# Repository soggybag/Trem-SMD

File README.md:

# Trem (SMD)

A tremolo for guitar in a Hammond 1590B: a TL064 LFO with SHAPE and SQ/TRI, driving a **discrete LM3086-style transistor VCA**. SMD parts are assembled by JLCPCB; the pots, toggle and LED are hand-soldered on the back (panel side).

## Controls

| Control | Part | Function |
|---|---|---|
| RATE | RV1 A10k | LFO speed, ~2–17 Hz (measured) |
| SHAPE | RV2 B100k | LFO skew: ramp up ↔ triangle ↔ ramp down |
| DEPTH | RV3 B100k | Tremolo depth, up to full cut |
| SQ/TRI | SW1 | Square or triangle LFO |
| Balance (trim) | RV4 2k (v2.1: symmetric, wiper to VA) | Nulls the LFO "thump" bleed |

Note: on this revision RATE and DEPTH turn backwards (fully CCW = fast / max) because the back-mounted pots mirror lugs 1 and 3. Fix planned for the next revision.

## How it works

- **LFO:** U1D integrator + U1C Schmitt trigger make the triangle and square. RATE sets the drive level; diodes D3/D4 with SHAPE set separate rise and fall rates.
- **Control:** DEPTH → U1A (inverting, offset by R13) sets the VCA tail current through R14.
- **Audio:** Q1 (MMBT5089) preamp → ÷48 → Q2 differential pair (gain ∝ tail current) → Q3 pair + Q4 PNP output amp → OUT.
- A reusable write-up of the VCA: [docs/VCA Building Block.md](docs/VCA%20Building%20Block.md).

Schematic: [Trem_23_schematic.pdf](Trem_23_schematic.pdf) · Layout: [Trem_23_layout.pdf](Trem_23_layout.pdf)

## Build notes

- **Hand-soldered (back side):** RATE/SHAPE/DEPTH 16 mm pots, SW1 (**sub-miniature** SPDT, 2.54 mm pitch, e.g. Taiway 200MSP1T1B1M1QE or Dailywell 2MS1; standard mini toggles do not fit), the LED, and the wire pads.
- Power: 9 V centre-negative; SS14 series reverse-polarity protection; ~3.2 mA (+ LED).
- Set RV4 for minimum LFO bleed at OUT (DEPTH max, no input, scope at 10 mV/div).
- Details: [docs/Build Notes.md](docs/Build%20Notes.md).

## Status

- Boards received from JLCPCB 2026-10-01; bench tested 2026-10-02. DC, LFO and VCA all verified, and it sounds good with a guitar. See [docs/Test Procedure.md](docs/Test%20Procedure.md).
- Next revision: bigger wiring pads or a 1×4 header, pot lug swap, RATE/DEPTH spacing (maybe 9 mm pots), toggle to the other side, LFO-rate LED idea. Roadmap: [Trem Roadmap.md](Trem%20Roadmap.md).

## Repository layout

```
Trem_23.kicad_pro / .kicad_sch / .kicad_pcb / .kicad_dru   KiCad 10 project
Trem.pretty/, fp-lib-table                              project footprints
3dmodels/          pot, switch and enclosure models (${KIPRJMOD})
docs/              test procedure, build notes, VCA write-up
enclosure/         panel art (Affinity + PDF/SVG exports)
*.pdf, *.png       schematic, layout and renders
```

Opens with KiCad 10. Libraries and 3D models are project-local or from KiCad's standard library.

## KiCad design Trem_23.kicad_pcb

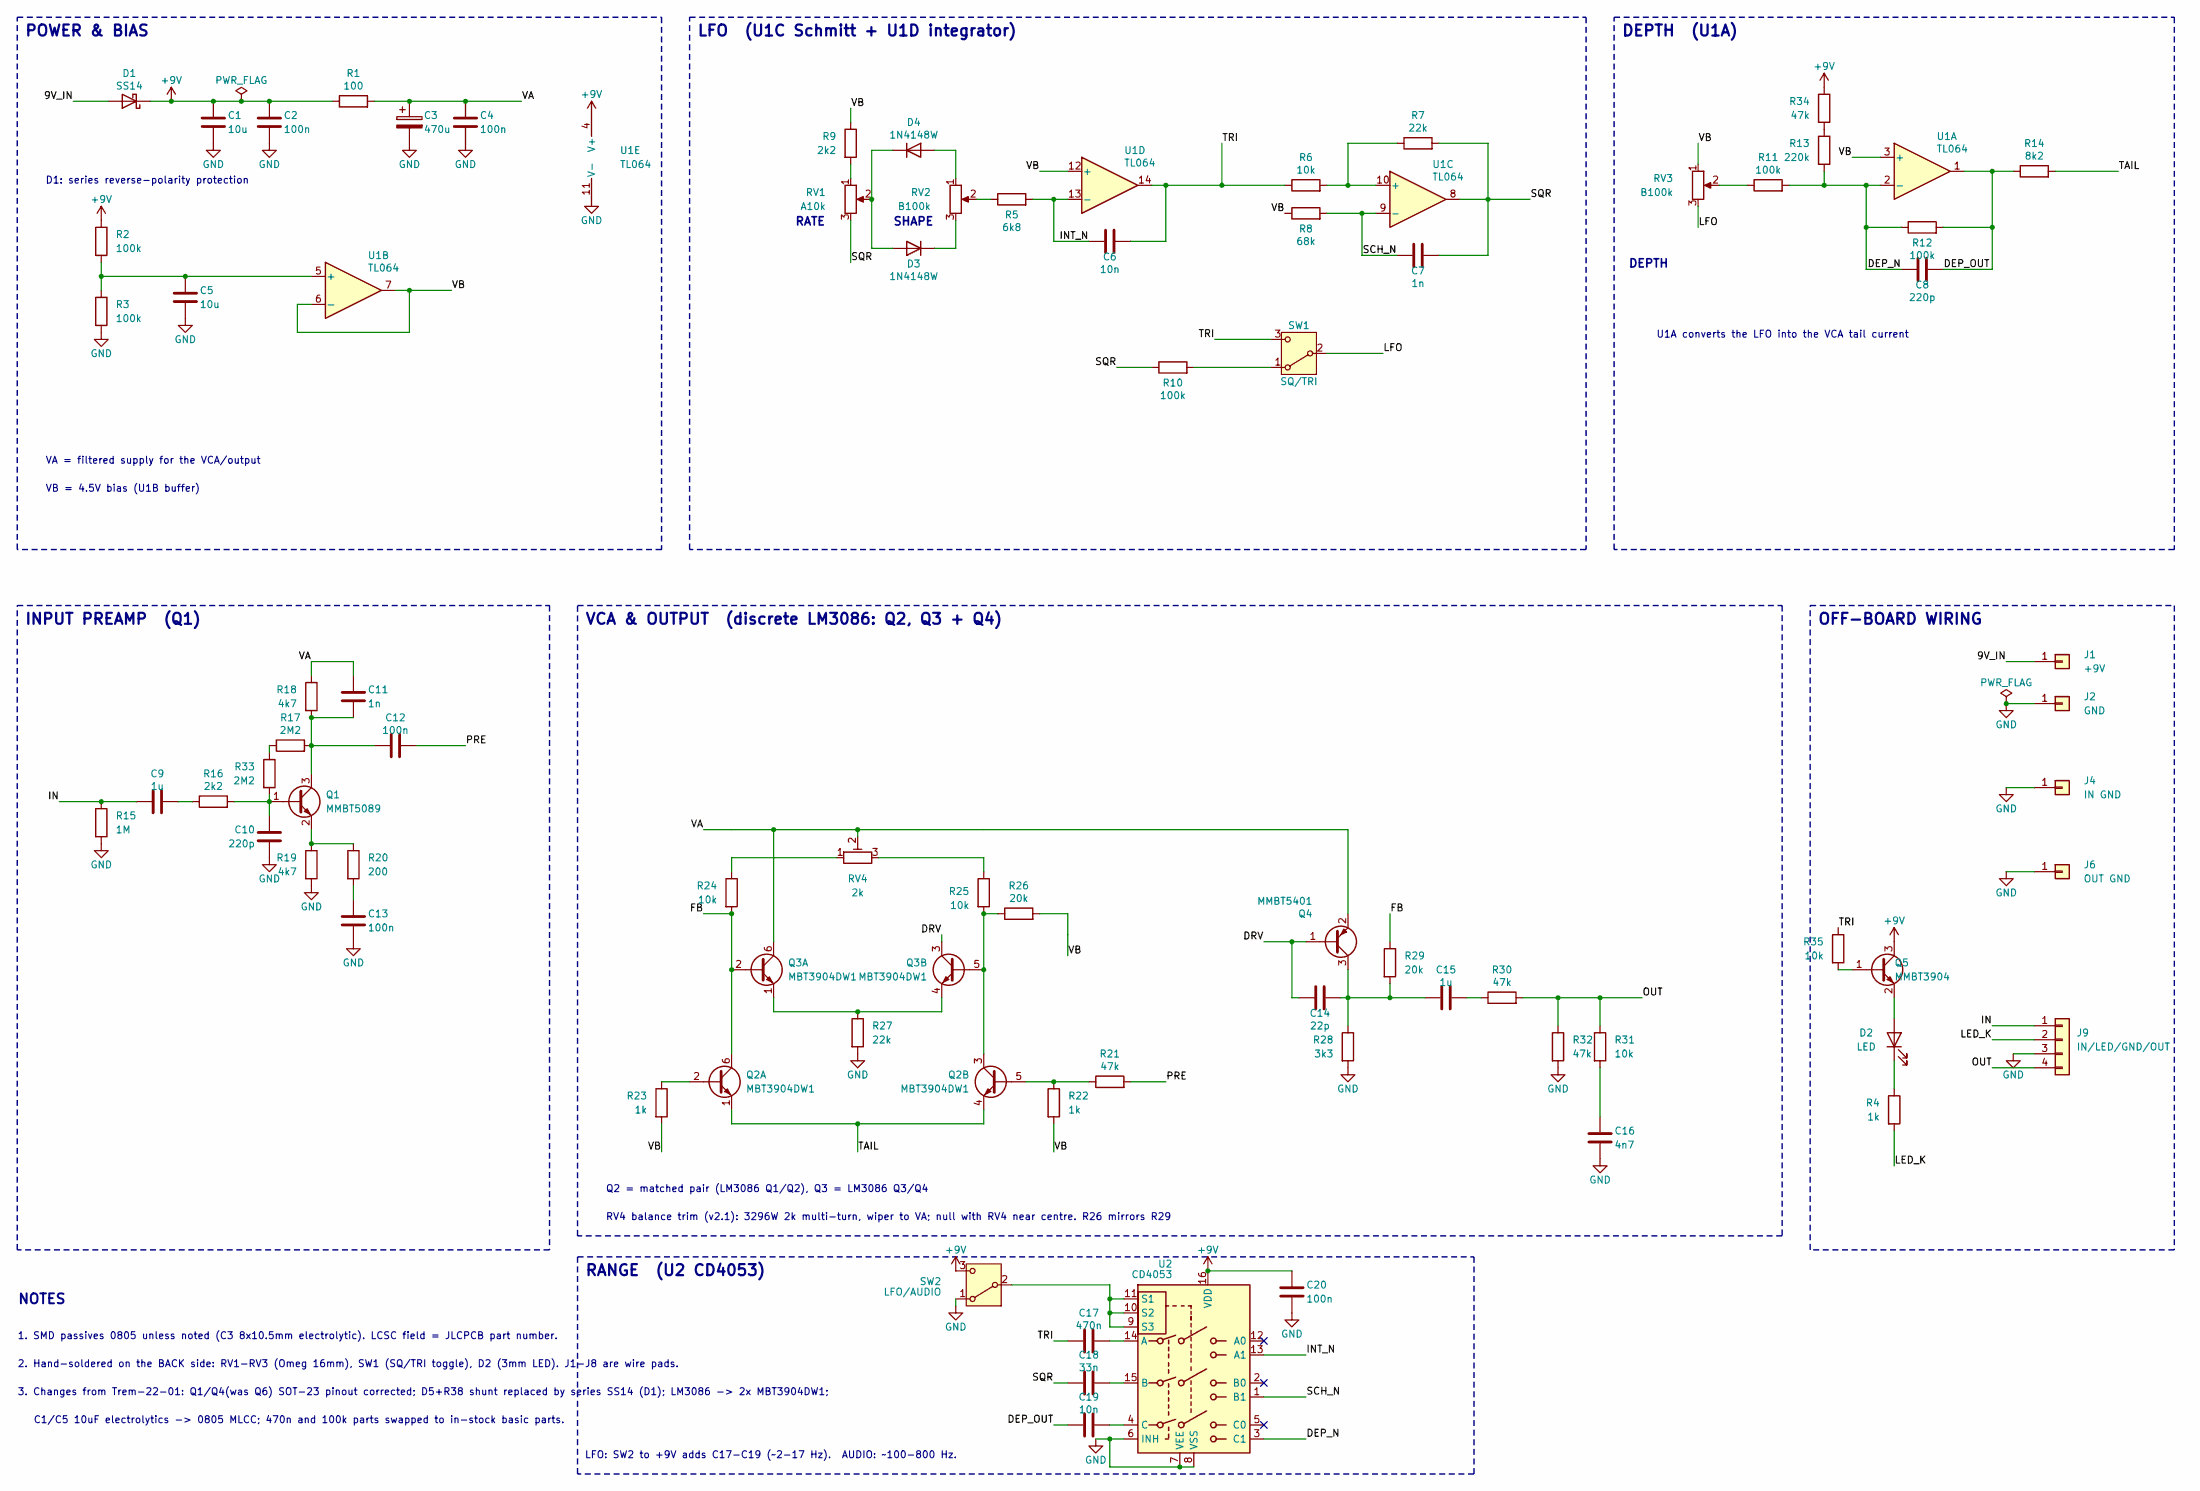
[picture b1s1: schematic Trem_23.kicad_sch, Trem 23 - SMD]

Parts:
C1, C5: 10u; C_0805_2012Metric; LCSC C15850
C2, C4, C12, C13: 100n; C_0805_2012Metric; LCSC C49678
C3: 470u; CP_Radial_D8.0mm_P3.50mm; LCSC C970706
C6: 10n; C_0805_2012Metric; LCSC C1710
C7, C11: 1n; C_0805_2012Metric; LCSC C46653
C8, C10: 220p; C_0805_2012Metric; LCSC C107145
C9, C15: 1u; C_0805_2012Metric; LCSC C28323
C14: 22p; C_0805_2012Metric; LCSC C1804
C16: 4n7; C_0805_2012Metric; LCSC C1744
C17: 470n; C_0805_2012Metric_Pad1.18x1.45mm_HandSolder; LCSC C13967
C18: 33n; C_0805_2012Metric_Pad1.18x1.45mm_HandSolder; LCSC C1739
C19: 10n; C_0805_2012Metric_Pad1.18x1.45mm_HandSolder; LCSC C1710
C20: 100n; C_0805_2012Metric_Pad1.18x1.45mm_HandSolder; LCSC C49678
D1: SS14; D_SMA; LCSC C2480
D2: LED; LED_D3.0mm
D3, D4: 1N4148W; D_SOD-123; LCSC C81598
J1: +9V; SolderWire-0.5sqmm_1x01_D0.9mm_OD2.1mm
J2: GND; SolderWire-0.5sqmm_1x01_D0.9mm_OD2.1mm
J4: IN GND; SolderWire-0.5sqmm_1x01_D0.9mm_OD2.1mm
J6: OUT GND; SolderWire-0.5sqmm_1x01_D0.9mm_OD2.1mm
J9: IN/LED/GND/OUT; PinHeader_1x04_P2.54mm_Vertical
Q1: MMBT5089; SOT-23; LCSC C116160
Q2, Q3: MBT3904DW1; SOT-363_SC-70-6; LCSC C110150
Q4: MMBT5401; SOT-23; LCSC C8326
Q5: MMBT3904; SOT-23; LCSC C20526
R1: 100; R_0805_2012Metric; LCSC C17408
R2, R3, R10, R11, R12: 100k; R_0805_2012Metric; LCSC C149504
R4, R22, R23: 1k; R_0805_2012Metric; LCSC C17513
R5: 6k8; R_0805_2012Metric; LCSC C17772
R6, R24, R25, R31: 10k; R_0805_2012Metric; LCSC C17414
R7, R27: 22k; R_0805_2012Metric; LCSC C17560
R8: 68k; R_0805_2012Metric; LCSC C17801
R9, R16: 2k2; R_0805_2012Metric; LCSC C17520
R13: 220k; R_0805_2012Metric; LCSC C17556
R14: 8k2; R_0805_2012Metric; LCSC C17828
R15: 1M; R_0805_2012Metric; LCSC C17514
R17: 2M2; R_0805_2012Metric; LCSC C26113
R18, R19: 4k7; R_0805_2012Metric; LCSC C17673
R20: 200; R_0805_2012Metric; LCSC C17540
R21, R30, R32: 47k; R_0805_2012Metric; LCSC C17713
R26, R29: 20k; R_0805_2012Metric; LCSC C4328
R28: 3k3; R_0805_2012Metric; LCSC C26010
R33: 2M2; R_0805_2012Metric_Pad1.20x1.40mm_HandSolder; LCSC C26113
R34: 47k; R_0805_2012Metric_Pad1.20x1.40mm_HandSolder; LCSC C17713
R35: 10k; R_0805_2012Metric_Pad1.20x1.40mm_HandSolder; LCSC C17414
RV1: A10k; Potentiometer_Alpha_RD901F-40-00D_Single_Vertical
RV2, RV3: B100k; Potentiometer_Alpha_RD901F-40-00D_Single_Vertical
RV4: 2k; Potentiometer_Bourns_3314J_Vertical; LCSC C94513
SW1: SQ/TRI; SW_Taiway_200_SPDT
SW2: LFO/AUDIO; SW_Taiway_200_SPDT
U1: TL064; SOIC-14_3.9x8.7mm_P1.27mm; LCSC C402159
U2: CD4053; SOIC-16_3.9x9.9mm_P1.27mm; LCSC C6742

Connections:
/9V_IN: D1.2 (A), J1.1
/DEP_N: C8.1, R11.2, R12.1, R13.2, U1.2 (-), U2.3 (C1)
/DEP_OUT: C8.2, C19.1, R12.2, R14.1, U1.1
/DRV: C14.1, Q3.3 (C2), Q4.1 (B)
/FB: Q2.6 (C1), Q3.2 (B1), R24.2, R29.1
/IN: C9.1, J9.1, R15.1
/INT_N: C6.1, R5.2, U1.13 (-), U2.13 (A1)
/LED_K: J9.2, R4.2
/LFO: RV3.3, SW1.2 (B)
/OUT: J9.4, R30.2, R31.1, R32.1
/PRE: C12.2, R21.2
/SCH_N: C7.1, R8.2, U1.9 (-), U2.1 (B1)
/SQR: C7.2, C18.1, R7.2, R10.1, RV1.3, U1.8
/TAIL: Q2.1 (E1), Q2.4 (E2), R14.2
/TRI: C6.2, C17.1, R6.1, R35.1, SW1.3 (C), U1.14
/VA: C3.1, C4.1, C11.1, Q3.6 (C1), Q4.2 (E), R1.2, R18.1, RV4.2
/VB: R8.1, R9.1, R22.2, R23.2, R26.2, RV3.1, U1.3 (+), U1.6 (-), U1.7, U1.12 (+)
unnamed: C9.2, R16.1
unnamed: C13.1, R20.2
unnamed: C15.2, R30.1
unnamed: C16.1, R31.2
unnamed: D2.2 (A), Q5.2 (E)
unnamed: D2.1 (K), R4.1
unnamed: D3.2 (A), D4.1 (K), RV1.2
unnamed: D3.1 (K), RV2.3
unnamed: D4.2 (A), RV2.1
unnamed: C10.1, Q1.1 (B), R16.2, R33.2
unnamed: C11.2, C12.1, Q1.3 (C), R17.2, R18.2
unnamed: Q1.2 (E), R19.1, R20.1
unnamed: Q2.2 (B1), R23.1
unnamed: Q2.5 (B2), R21.1, R22.1
unnamed: Q2.3 (C2), Q3.5 (B2), R25.2, R26.1
unnamed: Q3.1 (E1), Q3.4 (E2), R27.1
unnamed: C14.2, C15.1, Q4.3 (C), R28.1, R29.2
unnamed: Q5.1 (B), R35.2
unnamed: R5.1, RV2.2
unnamed: R9.2, RV1.1
unnamed: R11.1, RV3.2
unnamed: R13.1, R34.2
unnamed: R17.1, R33.1
unnamed: R24.1, RV4.1
unnamed: R25.1, RV4.3
unnamed: R10.2, SW1.1 (A)
unnamed: SW2.2 (B), U2.9 (S3), U2.10 (S2), U2.11 (S1)
unnamed: C5.1, R2.2, R3.1, U1.5 (+)
unnamed: R6.2, R7.1, U1.10 (+)
unnamed: C17.2, U2.14 (A)
unnamed: C18.2, U2.15 (B)
unnamed: C19.2, U2.4 (C)

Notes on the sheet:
C1/C5 10uF electrolytics -> 0805 MLCC; 470n and 100k parts swapped to in-stock basic parts.
DEPTH
1. SMD passives 0805 unless noted (C3 8x10.5mm electrolytic). LCSC field = JLCPCB part number.
DEPTH (U1A)
U1A converts the LFO into the VCA tail current
LFO (U1C Schmitt + U1D integrator)
OFF-BOARD WIRING
D1: series reverse-polarity protection
VCA & OUTPUT (discrete LM3086: Q2, Q3 + Q4)
POWER & BIAS
NOTES
SHAPE
INPUT PREAMP (Q1)
2. Hand-soldered on the BACK side: RV1-RV3 (Omeg 16mm), SW1 (SQ/TRI toggle), D2 (3mm LED). J1-J8 are wire pads.
Q2 = matched pair (LM3086 Q1/Q2), Q3 = LM3086 Q3/Q4
VA = filtered supply for the VCA/output
RATE
VB = 4.5V bias (U1B buffer)
RV4 balance trim (v2.1): 3296W 2k multi-turn, wiper to VA; null with RV4 near centre. R26 mirrors R29
3. Changes from Trem-22-01: Q1/Q4(was Q6) SOT-23 pinout corrected; D5+R38 shunt replaced by series SS14 (D1); LM3086 -> 2x MBT3904DW1;
RANGE (U2 CD4053)
LFO: SW2 to +9V adds C17-C19 (~2-17 Hz). AUDIO: ~100-800 Hz.

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
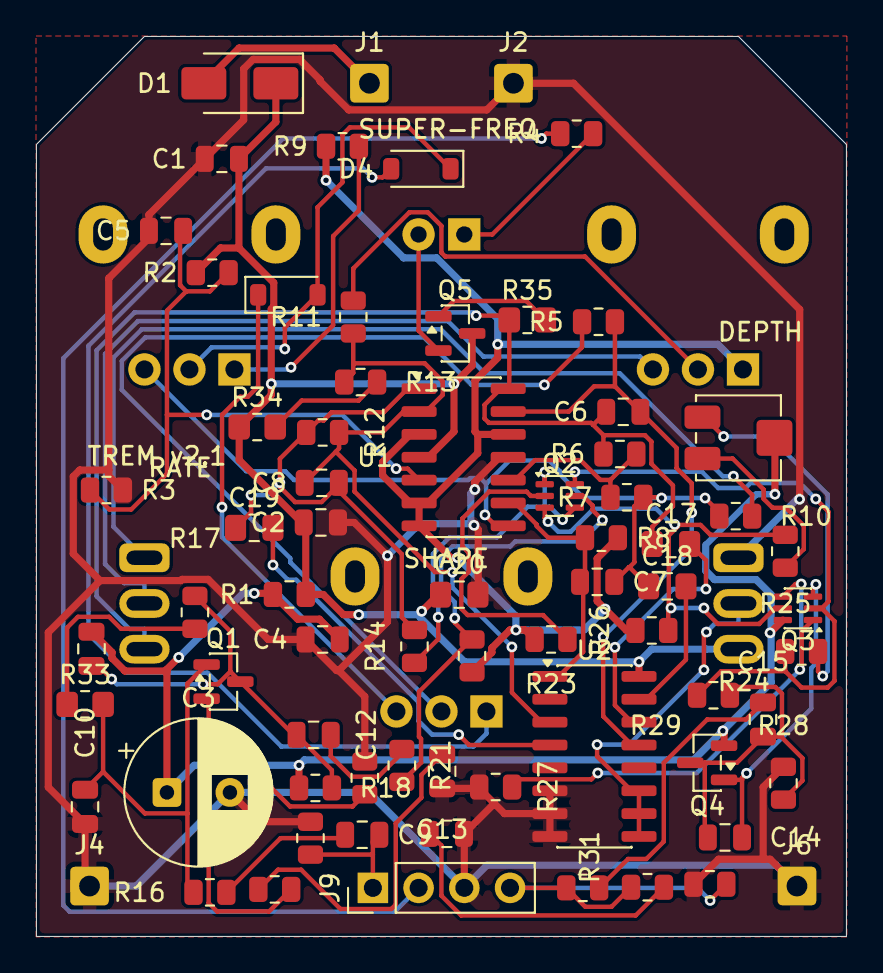
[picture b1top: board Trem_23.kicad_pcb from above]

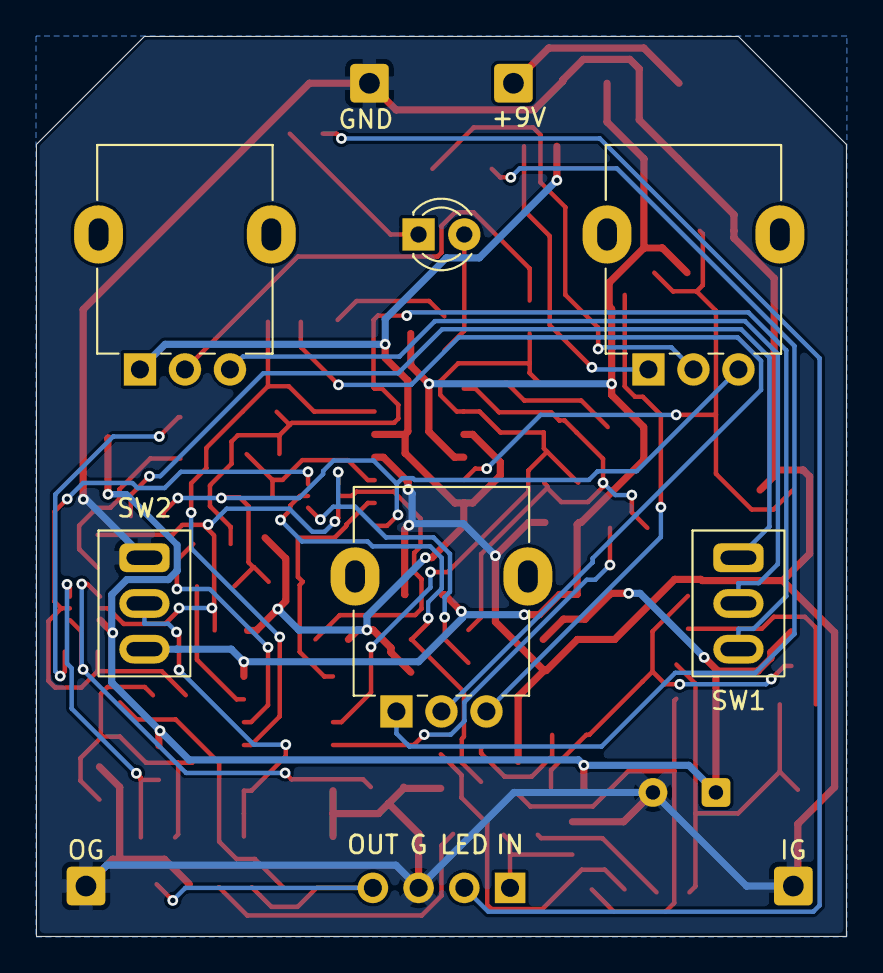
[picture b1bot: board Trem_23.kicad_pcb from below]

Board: 2 copper layers, 45.0 x 50.0 mm, 78 parts (7 on the bottom side), 51 nets.

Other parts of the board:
ENC1: Hammond 1590B; Hammond_1590B
